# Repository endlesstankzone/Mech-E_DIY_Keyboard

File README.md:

# Mech-E_DIY_Keyboard
Design a open source, custom layout, mechanical keyboard compatable with QMK firmware

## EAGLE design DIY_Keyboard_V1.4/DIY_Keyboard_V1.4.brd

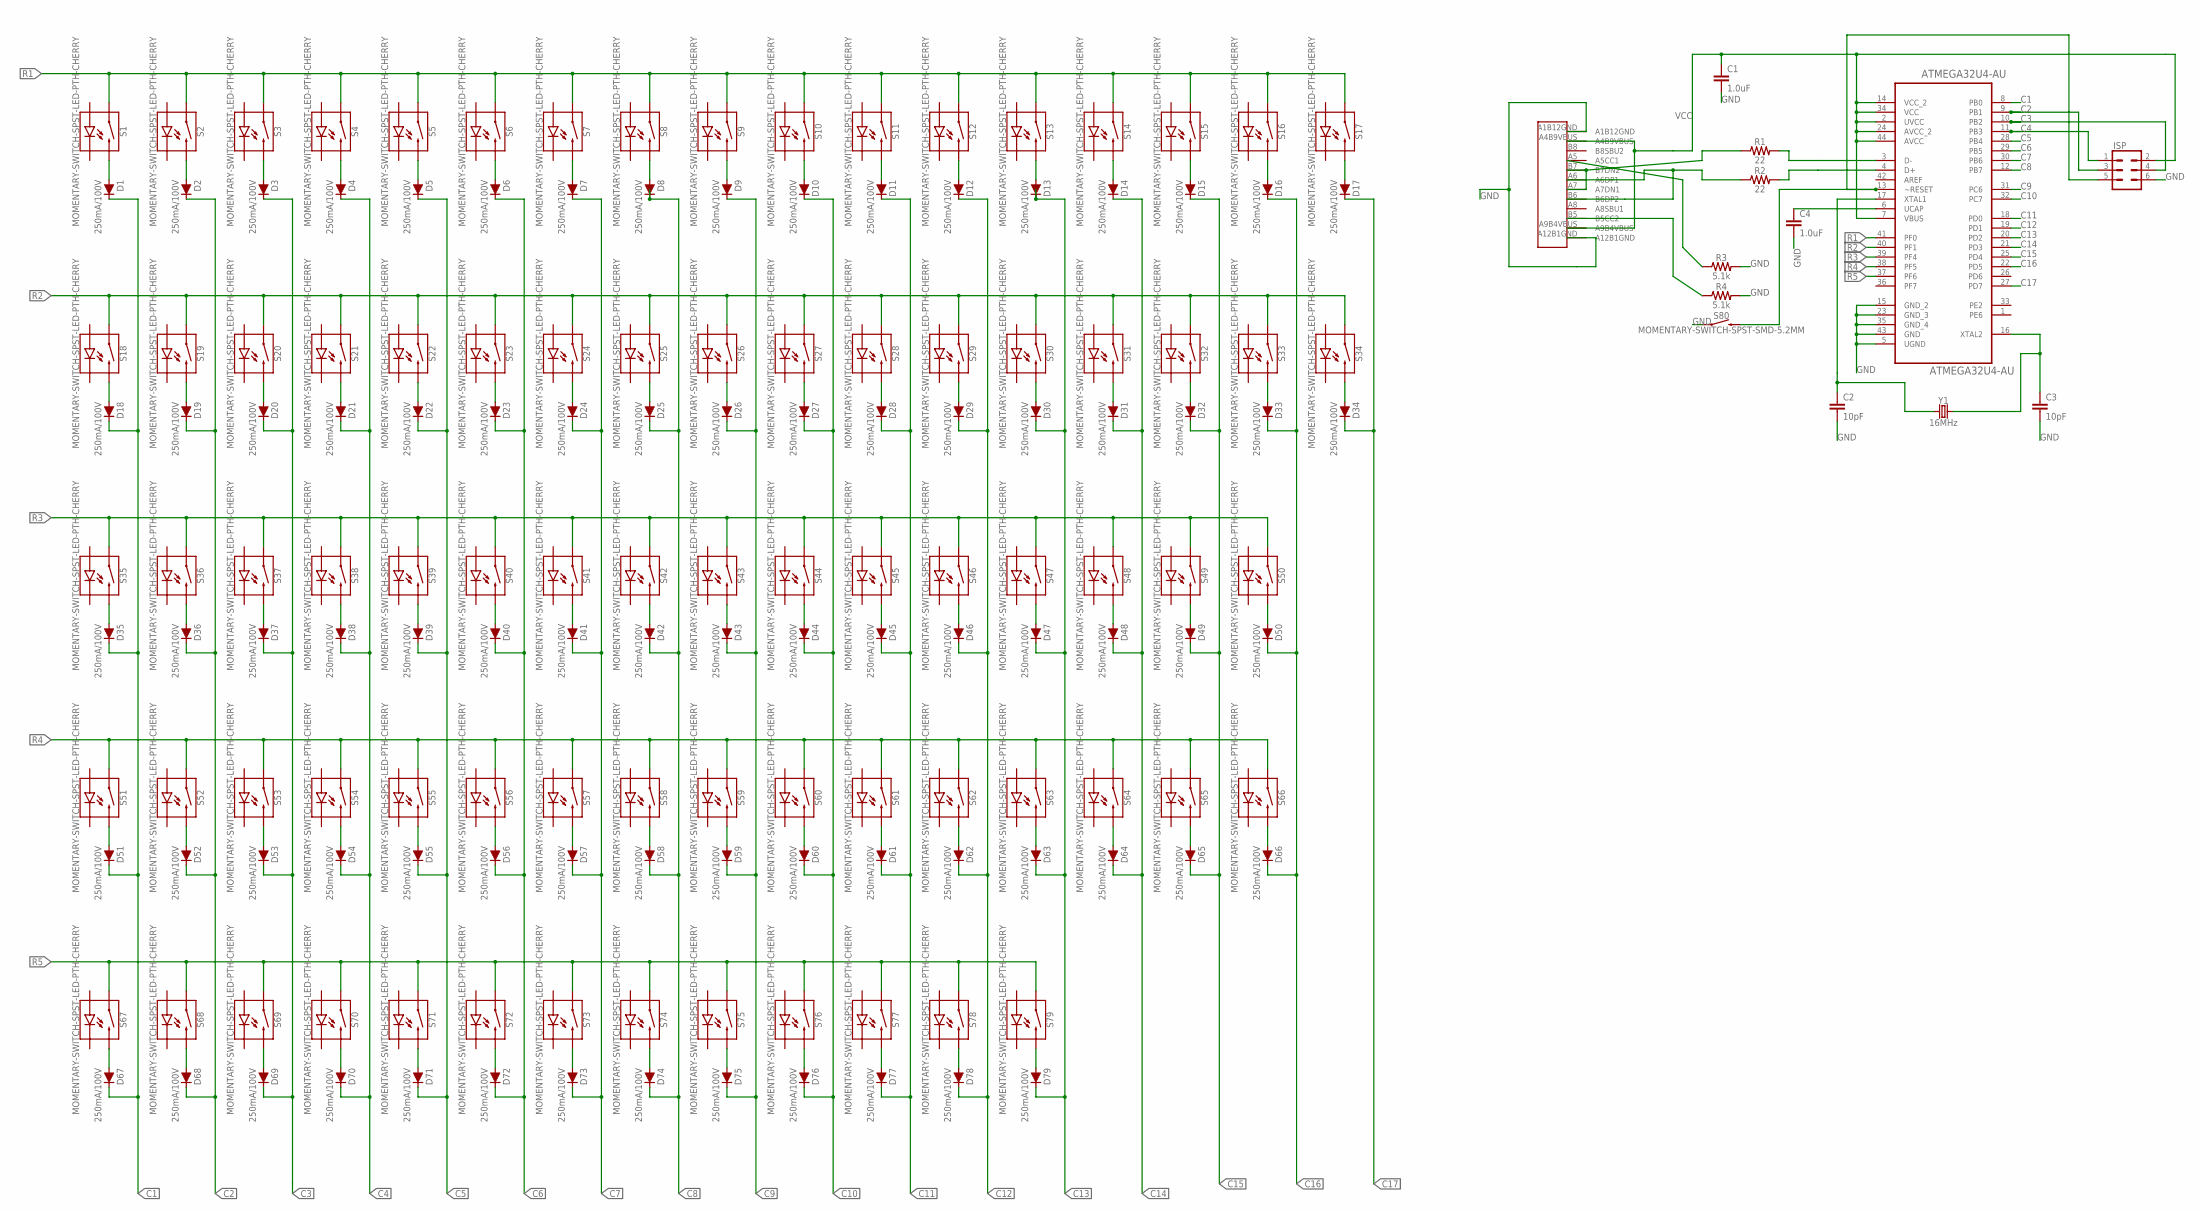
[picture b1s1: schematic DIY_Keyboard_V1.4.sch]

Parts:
ATMEGA32U4-AU: ATMEGA32U4-AU; QFP80P1200X1200X120-44N
C1, C4: 1.0uF; 0603
C2, C3: 10pF; 0603
D1, D2, D3, D4, D5, D6, D7, D8, D9, D10, D11, D12, D13, D14, D15, D16, D17, D18, D19, D20, D21, D22, D23, D24, D25, D26, D27, D28, D29, D30, D31, D32, D33, D34, D35, D36, D37, D38, D39, D40, D41, D42, D43, D44, D45, D46, D47, D48, D49, D50, D51, D52, D53, D54, D55, D56, D57, D58, D59, D60, D61, D62, D63, D64, D65, D66, D67, D68, D69, D70, D71, D72, D73, D74, D75, D76, D77, D78, D79: 250mA/100V; SOD-323
ISP: CONN_03X2FEMALE; 2X3
R1, R2: 22; 0603
R3, R4: 5.1k; 0603
S1, S2, S3, S4, S5, S6, S7, S8, S9, S10, S11, S12, S13, S14, S15, S16, S17, S18, S19, S20, S21, S22, S23, S24, S25, S26, S27, S28, S29, S30, S31, S32, S33, S34, S35, S36, S37, S38, S39, S40, S41, S42, S43, S44, S45, S46, S47, S48, S49, S50, S51, S52, S53, S54, S55, S56, S57, S58, S59, S60, S61, S62, S63, S64, S65, S66, S67, S68, S69, S70, S71, S72, S73, S74, S75, S76, S77, S78, S79: MOMENTARY-SWITCH-SPST-LED-PTH-CHERRY; CHERRY-MX-LED
S80: MOMENTARY-SWITCH-SPST-SMD-5.2MM; TACTILE_SWITCH_SMD_5.2MM
U$1: USB_TYPE_C
Y1: 16MHz; CRYSTAL-SMD-5X3.2-4PAD

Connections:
C1: ATMEGA32U4-AU.8 (PB0), D1.C, D18.C, D35.C, D51.C, D67.C
C2: ATMEGA32U4-AU.9 (PB1), D2.C, D19.C, D36.C, D52.C, D68.C, ISP.3
C3: ATMEGA32U4-AU.10 (PB2), D3.C, D20.C, D37.C, D53.C, D69.C, ISP.4
C4: ATMEGA32U4-AU.11 (PB3), D4.C, D21.C, D38.C, D54.C, D70.C, ISP.1
C5: ATMEGA32U4-AU.28 (PB4), D5.C, D22.C, D39.C, D55.C, D71.C
C6: ATMEGA32U4-AU.29 (PB5), D6.C, D23.C, D40.C, D56.C, D72.C
C7: ATMEGA32U4-AU.30 (PB6), D7.C, D24.C, D41.C, D57.C, D73.C
C8: ATMEGA32U4-AU.12 (PB7), D8.C, D25.C, D42.C, D58.C, D74.C
C9: ATMEGA32U4-AU.31 (PC6), D9.C, D26.C, D43.C, D59.C, D75.C
C10: ATMEGA32U4-AU.32 (PC7), D10.C, D27.C, D44.C, D60.C, D76.C
C11: ATMEGA32U4-AU.18 (PD0), D11.C, D28.C, D45.C, D61.C, D77.C
C12: ATMEGA32U4-AU.19 (PD1), D12.C, D29.C, D46.C, D62.C, D78.C
C13: ATMEGA32U4-AU.20 (PD2), D13.C, D30.C, D47.C, D63.C, D79.C
C14: ATMEGA32U4-AU.21 (PD3), D14.C, D31.C, D48.C, D64.C
C15: ATMEGA32U4-AU.25 (PD4), D15.C, D32.C, D49.C, D65.C
C16: ATMEGA32U4-AU.22 (PD5), D16.C, D33.C, D50.C, D66.C
C17: ATMEGA32U4-AU.27 (PD7), D17.C, D34.C
GND: ATMEGA32U4-AU.5 (UGND), ATMEGA32U4-AU.15 (GND_2), ATMEGA32U4-AU.23 (GND_3), ATMEGA32U4-AU.35 (GND_4), ATMEGA32U4-AU.43 (GND), C1.2, C2.2, C3.2, C4.2, ISP.6, R3.2, R4.2, S80.1, U$1.A1B12GND, U$1.A12B1GND
unnamed: D1.A, S1.S2 (2)
unnamed: D2.A, S2.S2 (2)
unnamed: D3.A, S3.S2 (2)
unnamed: D4.A, S4.S2 (2)
unnamed: D5.A, S5.S2 (2)
unnamed: D6.A, S6.S2 (2)
unnamed: D7.A, S7.S2 (2)
unnamed: D8.A, S8.S2 (2)
unnamed: D9.A, S9.S2 (2)
unnamed: D10.A, S10.S2 (2)
unnamed: D11.A, S11.S2 (2)
unnamed: D12.A, S12.S2 (2)
unnamed: D13.A, S13.S2 (2)
unnamed: D14.A, S14.S2 (2)
unnamed: D15.A, S15.S2 (2)
unnamed: D16.A, S16.S2 (2)
unnamed: D17.A, S17.S2 (2)
unnamed: D18.A, S18.S2 (2)
unnamed: D19.A, S19.S2 (2)
unnamed: D20.A, S20.S2 (2)
unnamed: D21.A, S21.S2 (2)
unnamed: D22.A, S22.S2 (2)
unnamed: D23.A, S23.S2 (2)
unnamed: D24.A, S24.S2 (2)
unnamed: D25.A, S25.S2 (2)
unnamed: D26.A, S26.S2 (2)
unnamed: D27.A, S27.S2 (2)
unnamed: D28.A, S28.S2 (2)
unnamed: D29.A, S29.S2 (2)
unnamed: D30.A, S30.S2 (2)
unnamed: D31.A, S31.S2 (2)
unnamed: D32.A, S32.S2 (2)
unnamed: D33.A, S33.S2 (2)
unnamed: D34.A, S34.S2 (2)
unnamed: D35.A, S35.S2 (2)
unnamed: D36.A, S36.S2 (2)
unnamed: D37.A, S37.S2 (2)
unnamed: D38.A, S38.S2 (2)
unnamed: D39.A, S39.S2 (2)
unnamed: D40.A, S40.S2 (2)
unnamed: D41.A, S41.S2 (2)
unnamed: D42.A, S42.S2 (2)
unnamed: D43.A, S43.S2 (2)
unnamed: D44.A, S44.S2 (2)
unnamed: D45.A, S45.S2 (2)
unnamed: D46.A, S46.S2 (2)
unnamed: D47.A, S47.S2 (2)
unnamed: D48.A, S48.S2 (2)
unnamed: D49.A, S49.S2 (2)
unnamed: D50.A, S50.S2 (2)
unnamed: D51.A, S51.S2 (2)
unnamed: D52.A, S52.S2 (2)
unnamed: D53.A, S53.S2 (2)
unnamed: D54.A, S54.S2 (2)
unnamed: D55.A, S55.S2 (2)
unnamed: D56.A, S56.S2 (2)
unnamed: D57.A, S57.S2 (2)
unnamed: D58.A, S58.S2 (2)
unnamed: D59.A, S59.S2 (2)
unnamed: D60.A, S60.S2 (2)
unnamed: D61.A, S61.S2 (2)
unnamed: D62.A, S62.S2 (2)
unnamed: D63.A, S63.S2 (2)
unnamed: D64.A, S64.S2 (2)
unnamed: D65.A, S65.S2 (2)
unnamed: D66.A, S66.S2 (2)
unnamed: D67.A, S67.S2 (2)
unnamed: D68.A, S68.S2 (2)
unnamed: D69.A, S69.S2 (2)
unnamed: D70.A, S70.S2 (2)
unnamed: D71.A, S71.S2 (2)
unnamed: D72.A, S72.S2 (2)
unnamed: D73.A, S73.S2 (2)
unnamed: D74.A, S74.S2 (2)
unnamed: D75.A, S75.S2 (2)
unnamed: D76.A, S76.S2 (2)
unnamed: D77.A, S77.S2 (2)
unnamed: D78.A, S78.S2 (2)
unnamed: D79.A, S79.S2 (2)
unnamed: ATMEGA32U4-AU.3 (D-), R1.2
unnamed: ATMEGA32U4-AU.4 (D+), R2.2
unnamed: R1.1, U$1.A7 (A7DN1), U$1.B7 (B7DN2)
unnamed: R2.1, U$1.A6 (A6DP1), U$1.B6 (B6DP2)
unnamed: ATMEGA32U4-AU.13 (~RESET), ISP.5, S80.3 (2)
unnamed: ATMEGA32U4-AU.16 (XTAL2), C3.1, Y1.3 (2)
unnamed: ATMEGA32U4-AU.17 (XTAL1), C2.1, Y1.1
unnamed: R3.1, U$1.A5 (A5CC1)
unnamed: R4.1, U$1.B5 (B5CC2)
unnamed: ATMEGA32U4-AU.6 (UCAP), C4.1
R1: ATMEGA32U4-AU.41 (PF0), S1.S1 (1), S2.S1 (1), S3.S1 (1), S4.S1 (1), S5.S1 (1), S6.S1 (1), S7.S1 (1), S8.S1 (1), S9.S1 (1), S10.S1 (1), S11.S1 (1), S12.S1 (1), S13.S1 (1), S14.S1 (1), S15.S1 (1), S16.S1 (1), S17.S1 (1)
R2: ATMEGA32U4-AU.40 (PF1), S18.S1 (1), S19.S1 (1), S20.S1 (1), S21.S1 (1), S22.S1 (1), S23.S1 (1), S24.S1 (1), S25.S1 (1), S26.S1 (1), S27.S1 (1), S28.S1 (1), S29.S1 (1), S30.S1 (1), S31.S1 (1), S32.S1 (1), S33.S1 (1), S34.S1 (1)
R3: ATMEGA32U4-AU.39 (PF4), S35.S1 (1), S36.S1 (1), S37.S1 (1), S38.S1 (1), S39.S1 (1), S40.S1 (1), S41.S1 (1), S42.S1 (1), S43.S1 (1), S44.S1 (1), S45.S1 (1), S46.S1 (1), S47.S1 (1), S48.S1 (1), S49.S1 (1), S50.S1 (1)
R4: ATMEGA32U4-AU.38 (PF5), S51.S1 (1), S52.S1 (1), S53.S1 (1), S54.S1 (1), S55.S1 (1), S56.S1 (1), S57.S1 (1), S58.S1 (1), S59.S1 (1), S60.S1 (1), S61.S1 (1), S62.S1 (1), S63.S1 (1), S64.S1 (1), S65.S1 (1), S66.S1 (1)
R5: ATMEGA32U4-AU.37 (PF6), S67.S1 (1), S68.S1 (1), S69.S1 (1), S70.S1 (1), S71.S1 (1), S72.S1 (1), S73.S1 (1), S74.S1 (1), S75.S1 (1), S76.S1 (1), S77.S1 (1), S78.S1 (1), S79.S1 (1)
VCC: ATMEGA32U4-AU.2 (UVCC), ATMEGA32U4-AU.7 (VBUS), ATMEGA32U4-AU.14 (VCC_2), ATMEGA32U4-AU.24 (AVCC_2), ATMEGA32U4-AU.34 (VCC), ATMEGA32U4-AU.44 (AVCC), C1.1, ISP.2, U$1.A4B9VBUS, U$1.A9B4VBUS

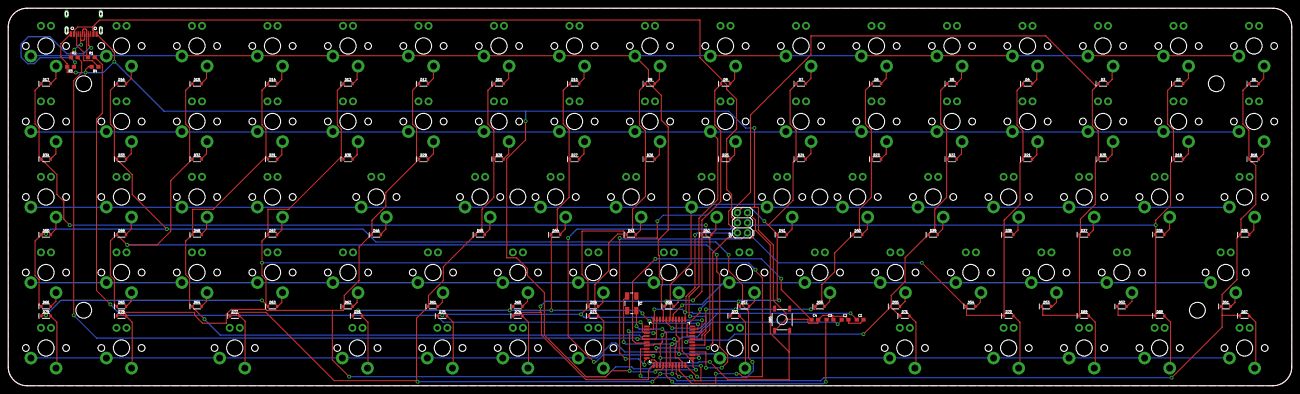
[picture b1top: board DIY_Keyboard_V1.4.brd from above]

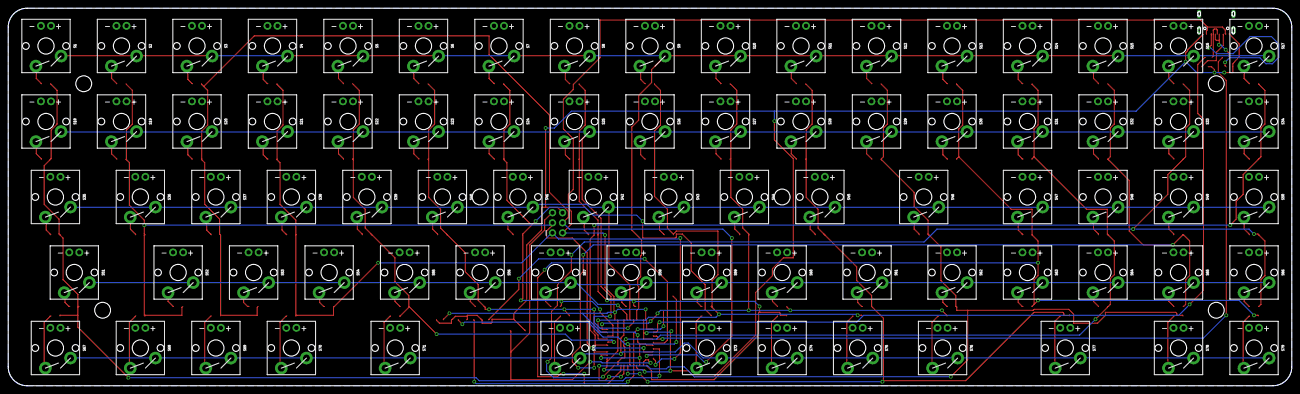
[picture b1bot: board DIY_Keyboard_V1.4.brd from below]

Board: 2 copper layers, 323.8 x 95.2 mm, 171 parts (79 on the bottom side), 113 nets.

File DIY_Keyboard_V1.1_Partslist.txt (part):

Partlist exported from C:/Users/tankh/Documents/GitHub/Mech-E_DIY_Keyboard/DIY_Keyboard_V1.1/DIY_Keyboard_V1.1.sch at 8/9/2019 9:44 AM

Qty Value                                Device                               Package                  Parts                                                                                                                                                                                                                                                                                                                                                                                            Description                                                                                                     AVAILABILITY DESCRIPTION                                                MF        MP            PACKAGE           PRICE PROD_ID    SF_ID     SF_SKU    VALUE     
1                                        CONN_03X2FEMALE                      2X3                      ISP                                                                                                                                                                                                                                                                                                                                                                                              Multi connection point. Often used as Generic Header-pin footprint for 0.1 inch spaced/style header connections                                                                                                                         CONN-11566                     FEMALE 2x3
2   1.0uF                                1.0UF-0603-16V-10%                   0603                     C1, C4                                                                                                                                                                                                                                                                                                                                                                                           1µF ceramic capacitors                                                                                                                                                                                                                  CAP-00868                      1.0uF     
2   10pF                                 10PF-0603-50V-5%                     0603                     C2, C3                                                                                                                                                                                                                                                                                                                                                                                           10pF ceramic capacitors                                                                                                                                                                                                                 CAP-11812                      10pF      
1   16MHz                                CRYSTAL-16MHZSMD-5X3.2               CRYSTAL-SMD-5X3.2-4PAD   Y1                                                                                                                                                                                                                                                                                                                                                                                               16MHz Crystal                                                                                                                                                                                                                           XTAL-08218 COM-00094           16MHz     
1   1k                                   1KOHM-0603-1/10W-1%                  0603                     R6                                                                                                                                                                                                                                                                                                                                                                                               1kΩ resistor                                                                                                                                                                                                                            RES-07856                      1k        
3   22                                   22OHM-0603-1/10W-1%                  0603                     R1, R2, R5                                                                                                                                                                                                                                                                                                                                                                                       22Ω resistor                                                                                                                                                                                                                            RES-08698                      22        
79  250mA/100V                           DIODE-BAS16J                         SOD-323                  D1, D2, D3, D4, D5, D6, D7, D8, D9, D10, D11, D12, D13, D14, D15, D16, D17, D18, D19, D20, D21, D22, D23, D24, D25, D26, D27, D28, D29, D30, D31, D32, D33, D34, D35, D36, D37, D38, D39, D40, D41, D42, D43, D44, D45, D46, D47, D48, D49, D50, D51, D52, D53, D54, D55, D56, D57, D58, D59, D60, D61, D62, D63, D64, D65, D66, D67, D68, D69, D70, D71, D72, D73, D74, D75, D76, D77, D78, D79 Diode                                                                                                                                                                                                                                   DIO-09646                      250mA/100V
2   5.1k                                 56KOHM                               0603                     R3, R4                                                                                                                                                                                                                                                                                                                                                                                                                                                                                                                                                                                                                                                                  56k       
2   56k                                  56KOHM                               0603                     R7, R8                                                                                                                                                                                                                                                                                                                                                                                                                                                                                                                                                                                                                                                                  56k       
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
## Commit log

2019-07-14 Uploaded initial files
2019-07-31 Updated Files
2019-08-03 Updated to version 1.1
2019-08-05 Updated connections
    Cleared all airwire and clearance errors
2019-08-05 Created reference board folder
    Moved all boards used during the design process.
2019-08-05 Created Datasheet folder
    Added all relavent datasheets to this folder
2019-08-05 Added 16mhz crystal datasheet for reference
2019-08-05 Added Atmega32u4 datasheet for reference
2019-08-05 Added USB-C datasheet for reference
2019-08-05 Moved all pictures and logos to pictures folder
2019-08-05 Created DXF folder
2019-08-05 Moved all SolidWorks files to there respective folder
2019-08-05 Created folder for custom eagle librarys
2019-08-09 Version 1.1 done!!
2019-08-09 Created Gerber files for manufacturing
2019-08-09 Added SparkFuns cam processor
2019-08-09 Updated Gerber files and created a custom cam processor
2019-08-09 Fixed spelling error
2019-08-15 Arduino compatible bootloaders
2019-08-15 Updated parts list
2019-08-15 Pinout for atmega32u4-au in arduino
2019-08-16 Updated to Version 1.2
    rounded corners
    removed new resistor land
2019-08-16 Uploaded keyboard firmware and configuration file
2020-02-10 Update keyboard layout
2020-02-10 Update Layout
2020-02-14 Uploaded case files
2020-02-14 Updated photo folder
2020-02-14 Uploaded keycap files
2020-02-15 Fixed number pad issues
2020-02-16 Updated to version 1.3
    removed caps lock led
2020-02-16 Export gerber files
2020-02-16 Update file names
2020-04-15 Create Keyboard_Layout_V2.SLDPRT
    Fixed spacing issues
2020-04-15 Update spacing
2020-04-15 create new version of keyboard
2020-04-15 Update board files
2020-04-15 added mirrored layout
2020-04-15 Updated missing line
2020-04-15 update board layout
2020-04-15 Working on pcb layout
2020-04-16 Updat layout
2020-04-16 Updated PCB Layout
2020-04-16 Export final CAM package
2020-04-17 remove mirrored sketch
2020-04-17 Update pcb layout and reexport gerber
2020-06-21 test assembly
2020-06-21 update cad files
2020-06-21 Update V1.4 CAD
2020-06-23 Added USB Port to board dummy
2020-06-23 Update assembly to include USB Port
2020-06-26 Update USB Port
2020-08-15 Created new version of chassis files
2020-08-15 Updated chasssis spacing and port location
2020-08-15 update chassis

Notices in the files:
parts and their libraries:
SparkFun-Capacitors: Licensing: Creative Commons ShareAlike 4.0 International - https://creativecommons.org/licenses/by-sa/4.0
